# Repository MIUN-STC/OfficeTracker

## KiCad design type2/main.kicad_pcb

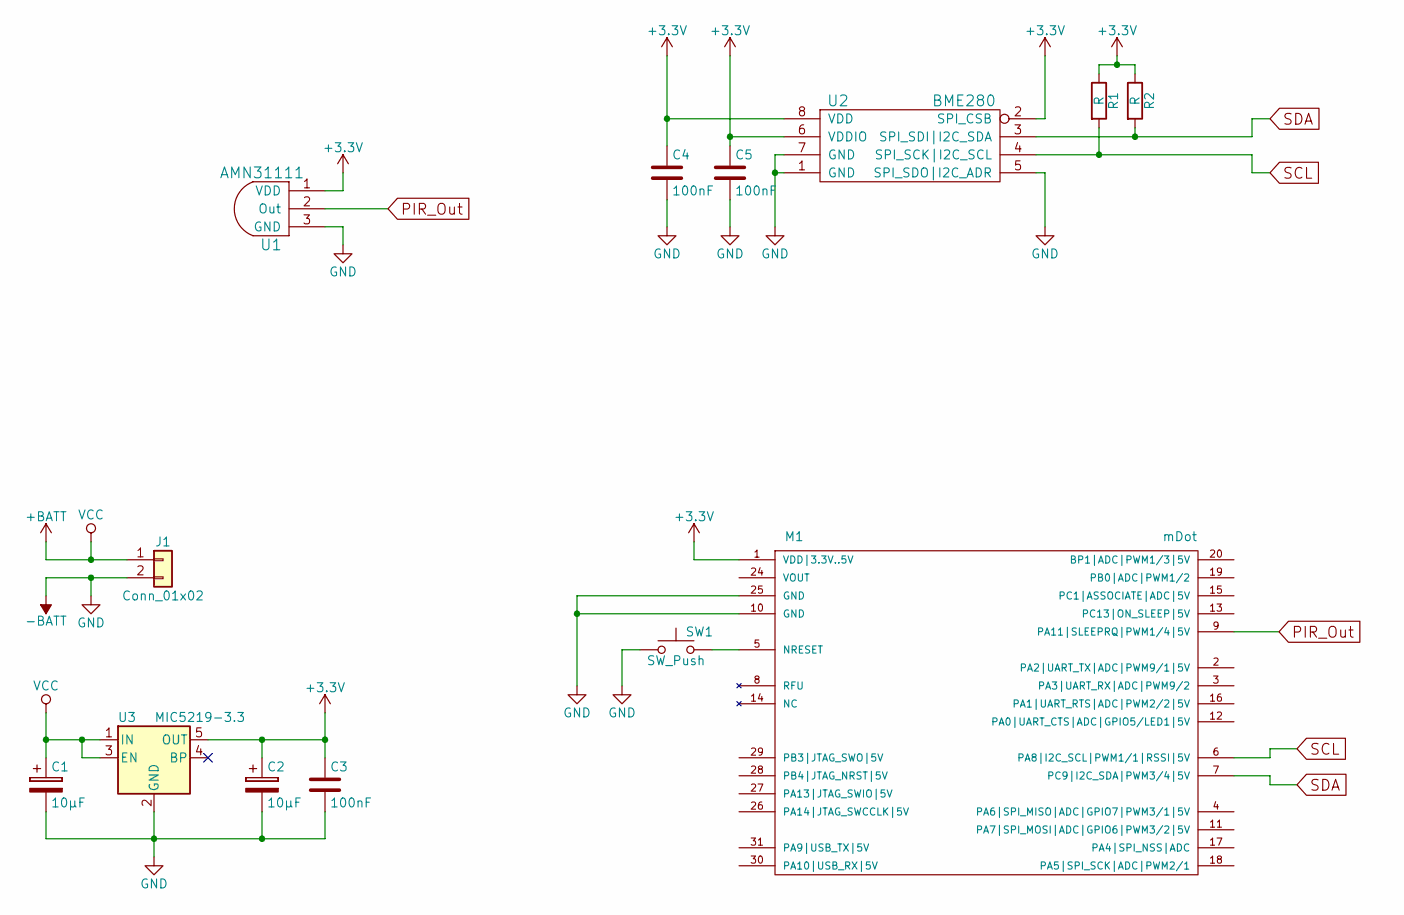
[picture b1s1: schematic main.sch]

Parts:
C1, C2: 10µF; C_1206
C3, C4, C5: 100nF; C_0603
J1: Conn_01x02; JST_PH_S2B-PH-K_02x2.00mm_Angled
M1: mDot
R1, R2: R; R_0603
SW1: SW_Push; SW_PUSH_6mm
U1: AMN31111
U2: BME280
U3: MIC5219-3.3; SOT-23-5

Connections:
+3V3: C2.1, C3.1, C4.1, C5.1, M1.1 (VDD|3.3V..5V), R1.1, R2.1, U1.1 (VDD), U2.2 (SPI_CSB), U2.6 (VDDIO), U2.8 (VDD), U3.5 (OUT); also elsewhere on the board
+BATT: C1.1, J1.1, U3.1 (IN), U3.3 (EN)
-BATT: C1.2, C2.2, C3.2, C4.2, C5.2, J1.2, M1.10 (GND), M1.25 (GND), SW1.1, U1.3 (GND), U2.1 (GND), U2.5 (SPI_SDO|I2C_ADR), U2.7 (GND), U3.2 (GND); also elsewhere on the board
unnamed: M1.5 (NRESET), SW1.2
PIR_Out: M1.9 (PA11|SLEEPRQ|PWM1/4|5V), U1.2 (Out); also elsewhere on the board
SCL: M1.6 (PA8|I2C_SCL|PWM1/1|RSSI|5V), R1.2, U2.4 (SPI_SCK|I2C_SCL)
SDA: M1.7 (PC9|I2C_SDA|PWM3/4|5V), R2.2, U2.3 (SPI_SDI|I2C_SDA)

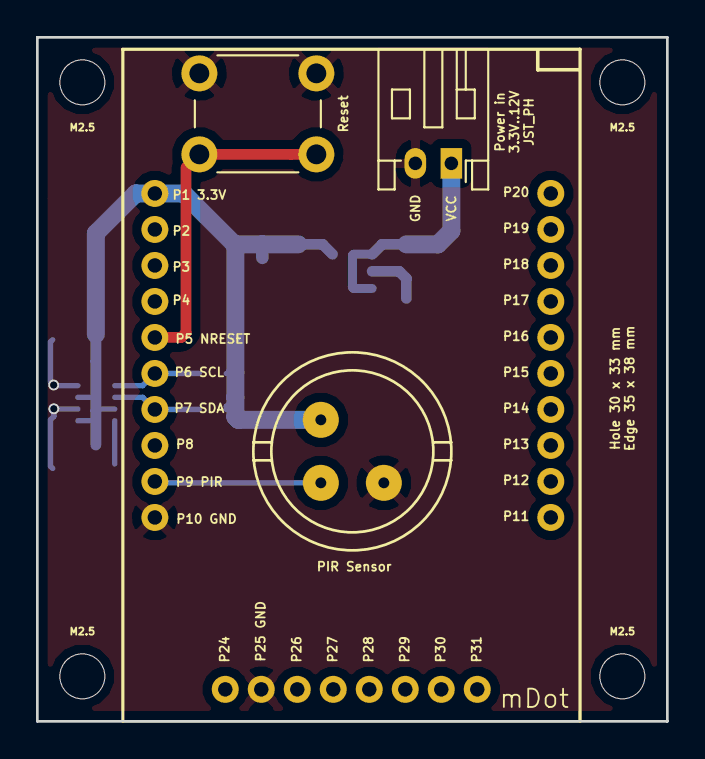
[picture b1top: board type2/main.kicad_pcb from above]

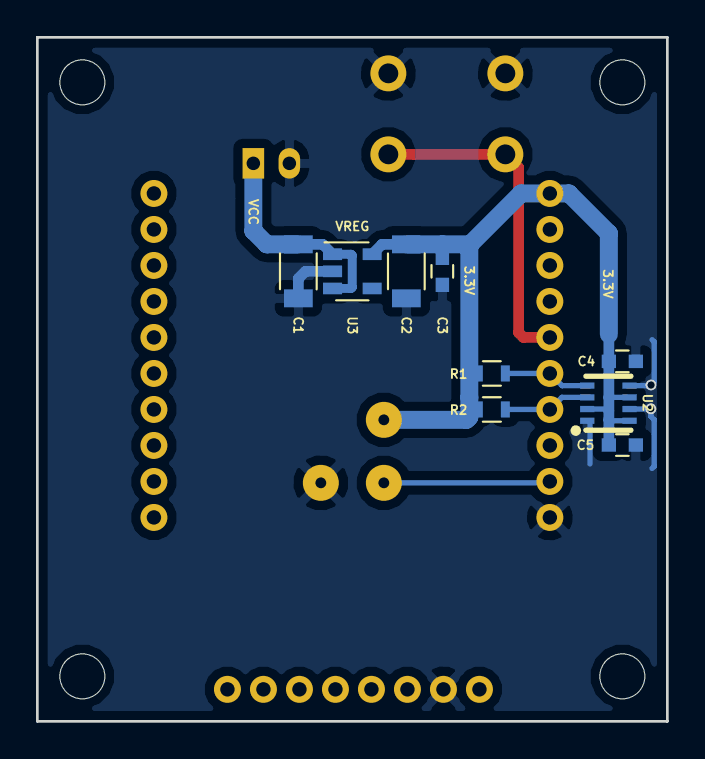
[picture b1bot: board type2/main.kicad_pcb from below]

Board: 2 copper layers, 35.0 x 38.0 mm, 17 parts (9 on the bottom side), 7 nets.

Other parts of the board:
H1, H2, H3, H4: MountingHole_2.5mm
PIR Sensor: AMN31111

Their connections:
+3V3: PIR Sensor.1; also elsewhere on the board
-BATT: PIR Sensor.3; also elsewhere on the board
PIR_Out: PIR Sensor.2; also elsewhere on the board

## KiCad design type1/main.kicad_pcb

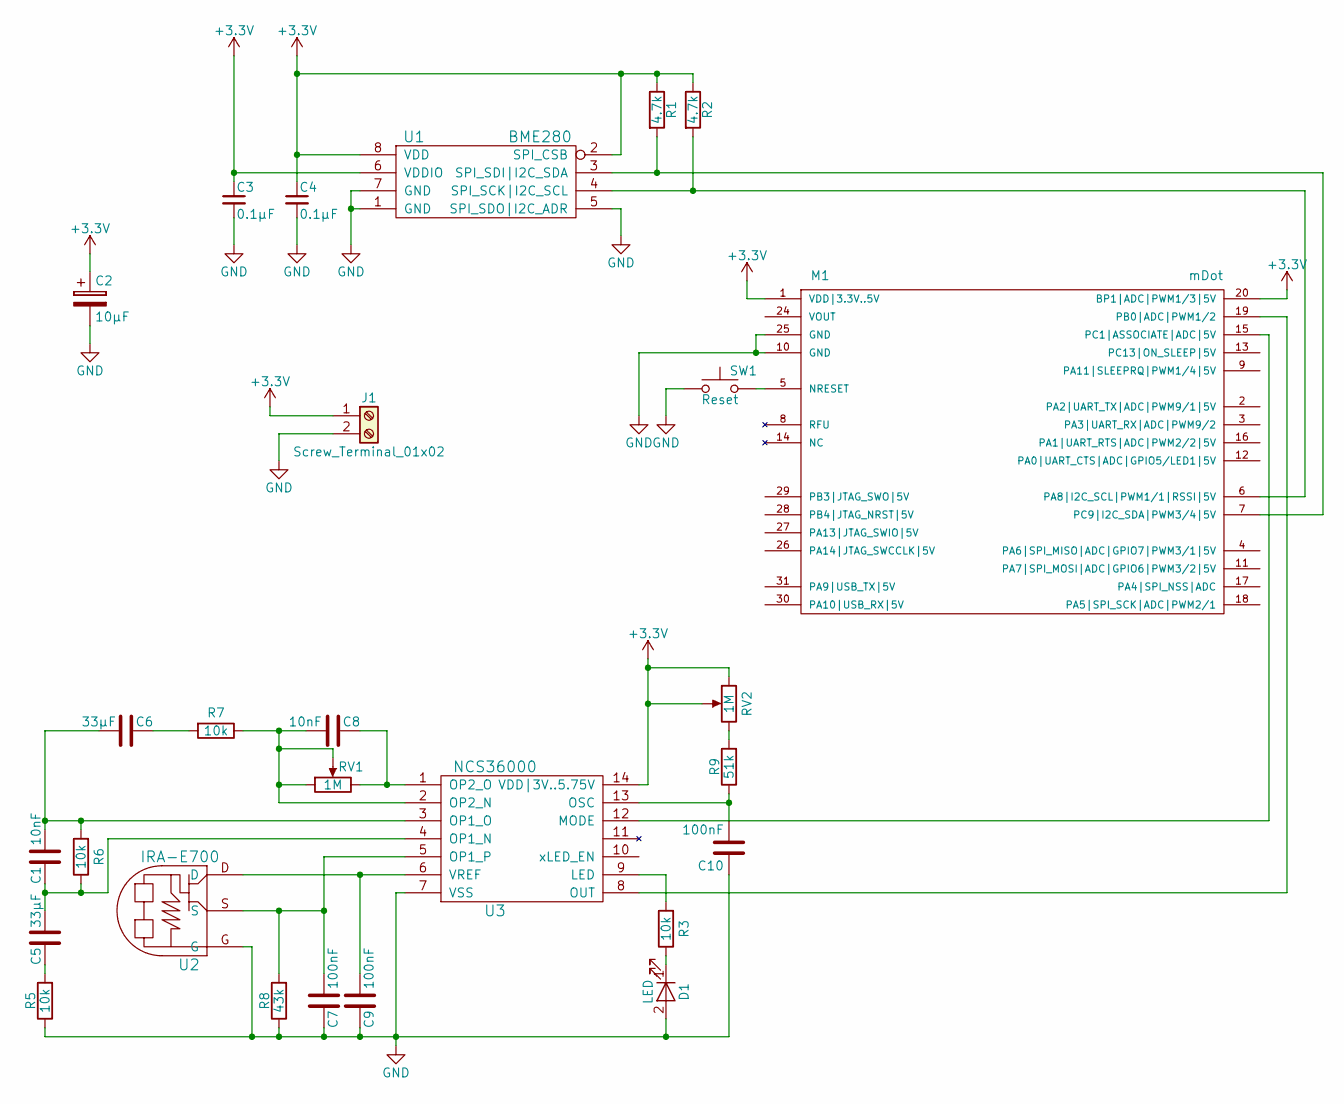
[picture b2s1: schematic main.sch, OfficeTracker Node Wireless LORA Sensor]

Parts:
C1, C8: 10nF; C_0402
C2: 10µF; CP_Elec_5x4.5
C3, C4: 0.1µF; C_0402
C5, C6: 33µF; C_0805
C7, C9, C10: 100nF; C_0402
D1: LED; LED_0603
J1: Screw_Terminal_01x02; TerminalBlock_Pheonix_MPT-2.54mm_2pol
M1: mDot
R1, R2: 4.7k; R_0402
R3, R5, R6, R7: 10k; R_0402
R8: 43k; R_0402
R9: 51k; R_0402
RV1, RV2: 1M; Potentiometer_Trimmer_Bourns_3296W
SW1: Reset; SW_PUSH_6mm_h5mm
U1: BME280
U2: IRA-E700
U3: NCS36000; SOIC-14_N

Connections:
+3V3: C2.1, C3.1, C4.1, J1.1, M1.1 (VDD|3.3V..5V), M1.20 (BP1|ADC|PWM1/3|5V), R1.1, R2.1, RV2.1, RV2.2, U1.2 (SPI_CSB), U1.6 (VDDIO), U1.8 (VDD), U3.14 (VDD|3V..5.75V)
GND: C2.2, C3.2, C4.2, C7.1, C9.1, C10.1, D1.2 (A), J1.2, M1.10 (GND), M1.25 (GND), R5.1, R8.1, SW1.1, U1.1 (GND), U1.5 (SPI_SDO|I2C_ADR), U1.7 (GND), U2.G, U3.7 (VSS)
unnamed: C1.1, C5.2, R6.1, U3.4 (OP1_N)
unnamed: C1.2, C6.2, R6.2, U3.3 (OP1_O)
unnamed: C5.1, R5.2
unnamed: C6.1, R7.2
unnamed: C7.2, R8.2, U2.S, U3.5 (OP1_P)
unnamed: C8.1, RV1.3, U3.1 (OP2_O)
unnamed: C8.2, R7.1, RV1.1, RV1.2, U3.2 (OP2_N)
unnamed: C9.2, U2.D, U3.6 (VREF)
unnamed: C10.2, R9.1, U3.13 (OSC)
unnamed: D1.1 (K), R3.1
unnamed: M1.5 (NRESET), SW1.2
unnamed: M1.6 (PA8|I2C_SCL|PWM1/1|RSSI|5V), R2.2, U1.4 (SPI_SCK|I2C_SCL)
unnamed: M1.7 (PC9|I2C_SDA|PWM3/4|5V), R1.2, U1.3 (SPI_SDI|I2C_SDA)
unnamed: M1.15 (PC1|ASSOCIATE|ADC|5V), U3.12 (MODE)
unnamed: M1.19 (PB0|ADC|PWM1/2), U3.8 (OUT)
unnamed: R3.2, U3.9 (LED)
unnamed: R9.2, RV2.3

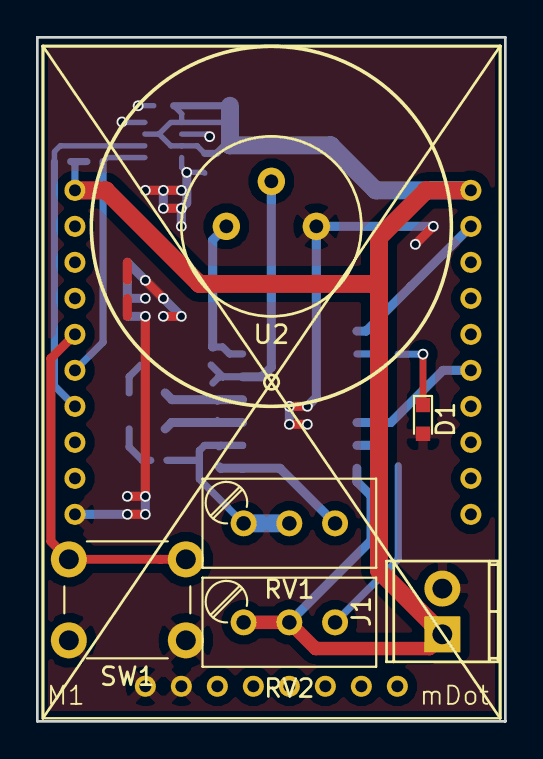
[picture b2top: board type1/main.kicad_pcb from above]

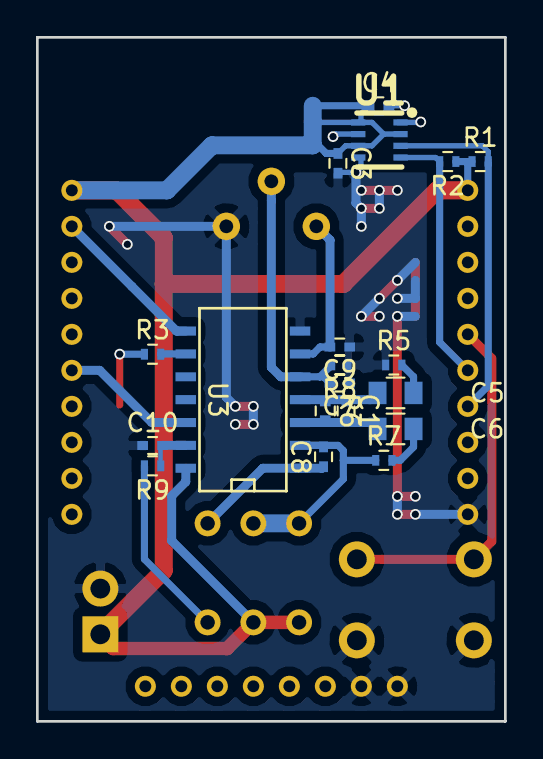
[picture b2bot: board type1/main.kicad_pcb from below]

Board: 2 copper layers, 26.0 x 38.0 mm, 26 parts (19 on the bottom side), 19 nets.

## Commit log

2017-09-13 :boom::camel: Added .gitattributes & .gitignore files
2017-09-14 test
2017-10-04 Improved design
